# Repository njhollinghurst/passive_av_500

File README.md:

# Passive A/V example circuit for Raspberry Pi 500

**This is the through-hole version, for easy hand assembly.** See the main branch for the original SMD version.

This simple circuit demonstrates composite video and audio out from Raspberry Pi 5 series computers, using only passive components (it cannot produce composite video from Raspberry Pi 400 or earlier models).  Audio quality is limited: some power supply noise may be audible. The circuit is nevertheless useful for less-demanding applications.

This is not an official product. It has not undergone regulatory testing. But you can make and adapt it.

The [board](kicad) was designed using KiCad 9.0. [Production files](production) were generated using the JLCPCB plugin. They are provided without any warranty of correctness or manufacturability.

## Quick instructions

 * Ensure you can log in remotely, in case you end up with no display.
 * Edit `config.txt` to add:
   * `dtoverlay=vc4-kms-v3d,composite` (append `,composite` to the existing `vc4-kms-v3d` line, if present).
   * `dtoverlay=vec-gpio-pi5,gpio27`
   * `dtoverlay=audremap,pins_12_13`
   * `power_force_3v3_pwm=1`
 * Optionally, set a video mode in `cmdline.txt` (the default will be 704x432i NTSC).
 * Power off before connecting anything.
 * Connect to Raspberry Pi 500 or 500+, ensuring connector is centrally aligned and covers all header pins! Component side up.
 * or install vertically on a Raspberry Pi 5 or CM5IO header, with component side facing towards the Raspberry Pi's HDMI ports.
 * To get both audio and video through the jack socket, connect a jumper between VIDEO and SLEEVE pins.
 * Unplug HDMI before booting with composite video enabled.

No picture? You might not have the new overlay. Type this (after Ctrl-Alt-T if using the GUI):

```
   pinctrl 4-11,27 a1
```

## Circuit notes

Here are the [schematic](images/schematic.pdf) and [list of components](production/bom.csv).

### Video

On the RP1 chip, three copies of an 8-bit signal from the VEC (video encoder) can be brought out to GPIO pins 4-27, with an optional clock on GPIO 0 (rather like DPI). It is usually clocked at 108 MHz.

Here we use a simple 7-bit resistor DAC. To improve linearity, the MSB is driven by two separate GPIOs (11 and 27).

Resistor values were chosen to approximate the sequence (490 x 2<sup><i>n</i></sup>) - 20 &Omega;. At least R1-R3, and preferably all resistors, should have 1% tolerance. More precise values for R5 and R7 might be 1.96 k&Omega;, 7.87 k&Omega;.

The output is DC-coupled with an impedance of about 125 &Omega;. Peak output is about 1.2 V into a 75 &Omega; load.

### Audio

This is a variant of the PWM filter used in some Raspberry Pi models, omitting the regulator and buffer for simplicity. Although intended for use with a TV or amplifier, it can (quietly) drive headphones with impedance &ge; 32 &Omega;.

C1, C3 footprints suit radial electrolytic capacitors with 2mm lead spacing. 20% tolerance and 10 V rating are fine.

### Connectors

J2 is Same Sky RCJ-014, available from DigiKey. Other sockets exist with similar footprints.

J4 is Tensility 54-00174. There are other similar-shaped TRRS sockets (some bending of pins may be required).

J3 is a 5-pin header, for testing and to make the video->J4 connection optional (otherwise, headphones could short the video signal). You could hard-wire a link here to omit J2, J3 and use only J4.

J1 is a 2.54mm 2x20 right-angle (horizontal) socket (female). This unusual choice was made with Raspberry Pi 500 in mind. Do **not** fit a socket on the underside! You would have to change the layout to adapt the board to HAT form factor.

### A note on missing footprints

The repository does not include any footprint or symbol libraries. Footprints for J2 and J4 are available from SnapMagic Search, Inc.

Note that I **changed their pin numbers** to match KiCad's symbols, trimmed silkscreen at board edges, and modified KiCad's `Raspberry_Pi_2_3` symbol to separate the GND pins.

## Version history

**2.0** First published SMD version. Added tooling holes. Tested, works well.

**2.1** Add ground plane vias. Increase audio resistors, to reduce GPIO peak current (slightly reducing audio level). Move J2 slightly.

**thru-hole/th-1.0** (untested). Through-hole version with different footprints and some component tweaks. C1, C3 replaced by electrolytic capacitors. R10, R12 changed to 270 &Omega; for availability.

**thru-hole/th-1.1** (untested). Through-hole version. Remove unused layers (solder paste, adhesive). Change C1, C3 footprints to 2.0mm pin spacing.

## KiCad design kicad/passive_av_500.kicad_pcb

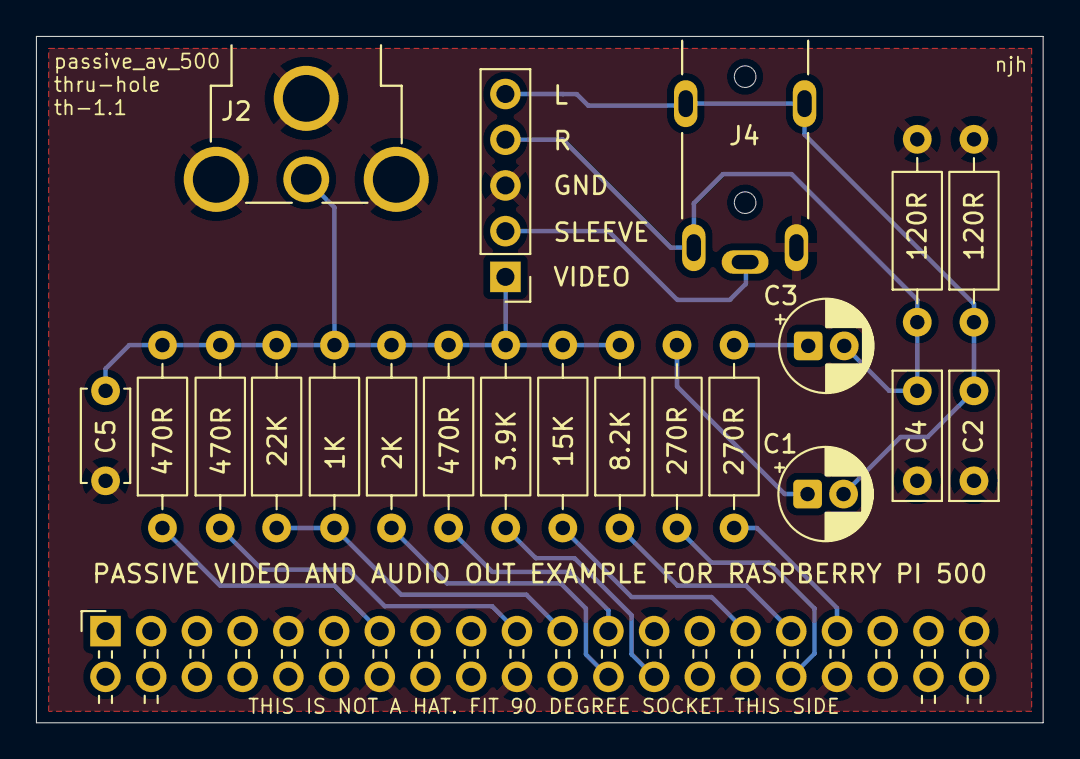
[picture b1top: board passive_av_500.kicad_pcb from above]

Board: 2 copper layers, 55.9 x 38.1 mm, 22 parts (0 on the bottom side), 17 nets.

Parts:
C1, C3: 22uF; CP_Radial_D5.0mm_P2.00mm
C2, C4: 100nF; C_Rect_L7.0mm_W2.5mm_P5.00mm
C5: 100pF; C_Disc_D5.0mm_W2.5mm_P5.00mm
J1: Raspberry_Pi_5; PinSocket_2x20_P2.54mm_Horizontal_trimsilk
J2: Conn_Coaxial; CUI_RCJ-014_Inner1Outer2_trimsilk
J3: Conn_01x05; PinHeader_1x05_P2.54mm_Vertical
J4: AudioJack4; TENSILITY_54-00174_TR1R2S_trimsilk
R1, R2, R3: 470R; R_Axial_DIN0207_L6.3mm_D2.5mm_P10.16mm_Horizontal
R4: 1K; R_Axial_DIN0207_L6.3mm_D2.5mm_P10.16mm_Horizontal
R5: 2K; R_Axial_DIN0207_L6.3mm_D2.5mm_P10.16mm_Horizontal
R6: 3.9K; R_Axial_DIN0207_L6.3mm_D2.5mm_P10.16mm_Horizontal
R7: 8.2K; R_Axial_DIN0207_L6.3mm_D2.5mm_P10.16mm_Horizontal
R8: 15K; R_Axial_DIN0207_L6.3mm_D2.5mm_P10.16mm_Horizontal
R9: 22K; R_Axial_DIN0207_L6.3mm_D2.5mm_P10.16mm_Horizontal
R10, R12: 270R; R_Axial_DIN0207_L6.3mm_D2.5mm_P10.16mm_Horizontal
R11, R13: 120R; R_Axial_DIN0207_L6.3mm_D2.5mm_P10.16mm_Horizontal

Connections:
/AUD_L: C1.2, C2.1, J3.5, J4.T, R11.1
/AUD_R: C3.2, C4.1, J3.4, J4.R1, R13.1
/VID: C5.1, J2.1 (In), J3.1, R1.2, R2.2, R3.2, R4.2, R5.2, R6.2, R7.2, R8.2, R9.2
GND: C2.2, C4.2, C5.2, J1.9 (GND), J1.14 (GND), J1.20 (GND), J1.25 (GND), J1.30 (GND), J1.34 (GND), J1.39 (GND), J2.2 (Ext), J3.3, J4.R2, R11.2, R13.2
unnamed: C1.1, R10.2
unnamed: C3.1, R12.2
unnamed: J1.29 (GCLK1/GPIO5), R8.1
unnamed: J1.31 (GCLK2/GPIO6), R7.1
unnamed: J1.13 (GPIO27), R2.1
unnamed: J1.21 (MISO0/GPIO9), R4.1, R9.1
unnamed: J1.19 (MOSI0/GPIO10), R3.1
unnamed: J1.32 (PWM0/GPIO12), R10.1
unnamed: J1.33 (PWM1/GPIO13), R12.1
unnamed: J1.23 (SCLK0/GPIO11), R1.1
unnamed: J1.24 (~CE0/GPIO8), R5.1
unnamed: J1.26 (~CE1/GPIO7), R6.1
unnamed: J3.2, J4.S

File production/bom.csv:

Designator,Footprint,Quantity,Value
"C1, C3",CP_Radial_D6.3mm_P2.50mm,2,22uF
"C2, C4",C_Rect_L7.0mm_W2.5mm_P5.00mm,2,100nF
C5,C_Disc_D5.0mm_W2.5mm_P5.00mm,1,100pF
J1,PinSocket_2x20_P2.54mm_Horizontal_trimsilk,1,Raspberry_Pi_5
J2,CUI_RCJ-014_Inner1Outer2_trimsilk,1,Conn_Coaxial
J3,PinHeader_1x05_P2.54mm_Vertical,1,Conn_01x05
J4,TENSILITY_54-00174_TR1R2S_trimsilk,1,AudioJack4
"R1, R2, R3",R_Axial_DIN0207_L6.3mm_D2.5mm_P10.16mm_Horizontal,3,470R
"R10, R12",R_Axial_DIN0207_L6.3mm_D2.5mm_P10.16mm_Horizontal,2,270R
"R11, R13",R_Axial_DIN0207_L6.3mm_D2.5mm_P10.16mm_Horizontal,2,120R
R4,R_Axial_DIN0207_L6.3mm_D2.5mm_P10.16mm_Horizontal,1,1K
R5,R_Axial_DIN0207_L6.3mm_D2.5mm_P10.16mm_Horizontal,1,2K
R6,R_Axial_DIN0207_L6.3mm_D2.5mm_P10.16mm_Horizontal,1,3.9K
R7,R_Axial_DIN0207_L6.3mm_D2.5mm_P10.16mm_Horizontal,1,8.2K
R8,R_Axial_DIN0207_L6.3mm_D2.5mm_P10.16mm_Horizontal,1,15K
R9,R_Axial_DIN0207_L6.3mm_D2.5mm_P10.16mm_Horizontal,1,22K

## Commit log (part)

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2025-10-29 Candidate files for "Rev 2" prototype - not yet tested
2025-10-29 Add some images generated by KiCad
2025-10-30 README: add notes on "production" files
2025-10-30 Add "tooling holes" and reconnect J1 pin 39 to improve GND plane
2025-10-30 Add production files
2025-10-31 Add LICENSE file (CC0)
2025-11-06 README.md: improve and tidy (squashed)
2025-11-06 Add vias to ground planes
    Mainly to shorten the return current paths of C2, C4 and C5.
2025-11-09 Candidate "rev 2.1" version
    Increase R10,R12 and R11,R13 to 300R and 120R. This will slightly
    reduce audio level, but ensures peak GPIO current is below 12mA
    and total can't exceed 50mA (even if all A/V outputs are shorted).
    Update README.md, images and production files.
